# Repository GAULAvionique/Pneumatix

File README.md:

<!--"""-->

<h1 align="center">Projet Pneumatix - GAUL 2024-2025</h1>

<p align="left">

</p>

## 🌟 **Projet Pneumatix**

Pneumatix est un **module de communication et de télémétrie séparé** développé par le GAUL pour assurer un relais de données fiable entre les systèmes embarqués de la fusée et la station au sol. Conçu comme une carte fille (PCB de communication) isolée du PCB principal, le système garantit une intégrité maximale des signaux RF.

Le projet est conçu pour être :

*   Performant sur de longues distances (Module LoRa 433MHz)
*   Modulable avec un contrôle matériel des états (M0/M1) manuellement
*   Robuste face aux interférences électromagnétiques et à l'effet Doppler

L’objectif principal de Pneumatix est d'assurer une liaison de télémétrie fiable (comparée au RFD900X).

---

## 📦 **Fonctionnalités Intégrées**

Le système centralise l'infrastructure de communication externe et inclut :

*   **Communication Radio LoRa**
    Intégration du module EBYTE E22-400T33S avec routage d'antenne SMA 50 ohms pour une portée maximale et gestion des canaux LBT (Listen Before Talk).
*   **Microcontrôleur (Optionnel / Déporté)**
    Interfaçage direct avec le STM32F4 de ODBlix via des signaux logiques 3.3V natifs ou possibilité de programmer seul.
*   **Contrôle de Mode Matériel**
    Configuration des modes de fonctionnement (Normal, WOR, Configuration, Veille) via des *solder jumpers* sur les broches M0 et M1.
*   **Indicateurs de statut**
    Diagnostic visuel via des LEDs dédiées pour l'alimentation 5V et l'état d'occupation du buffer série (broche AUX).

---

## 🛰 **Architecture du Projet**

Le dépôt contient l’ensemble des éléments matériels et logiciels nécessaires au déploiement du module :

*   Schémas de conception PCB (Routage RF)
*   Scripts de configuration des registres LoRa
*   Documentation technique

---

## 📚 **Documentation**

La documentation complète des pièces du projet est disponible dans le dossier `Documentation/`.

---

## ⚙ **Compilation et Déploiement**

Le code d'interfaçage est développé autour de l’écosystème ODBLix pour communiquer avec le module.

### Compilation

```bash
git clone [https://github.com/GAULAvionique/Pneumatix.git](https://github.com/GAULAvionique/Pneumatix.git)

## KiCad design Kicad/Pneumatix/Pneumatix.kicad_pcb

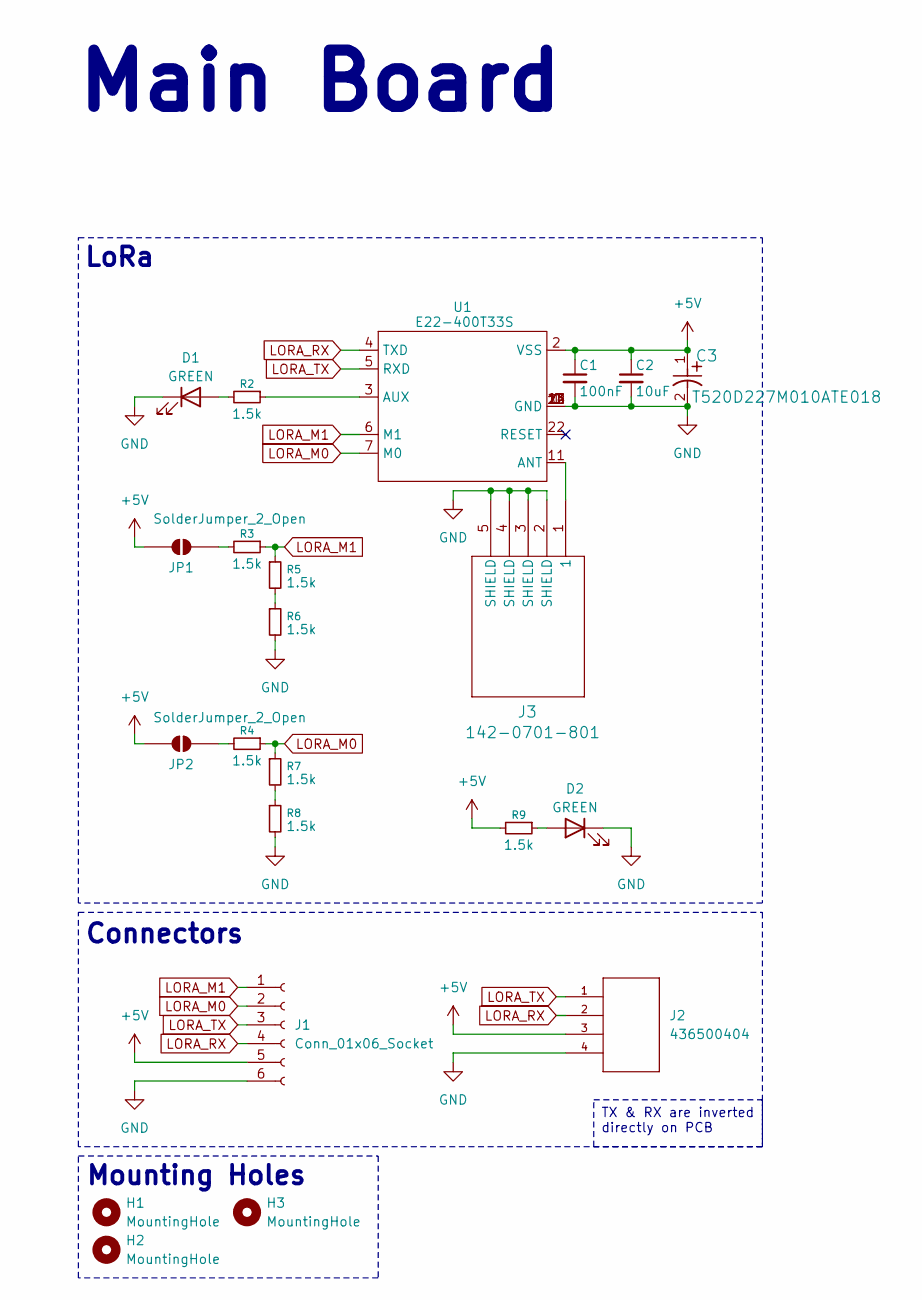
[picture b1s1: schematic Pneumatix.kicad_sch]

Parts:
C1: 100nF; C_0603_1608Metric; Manufacturer_Part_Number C0603C104K5RACTU; DigitKey_Part_Number 399-C0603C104K5RACTUCT-ND
C2: 10uF; C_0603_1608Metric; Manufacturer_Part_Number LMK107BBJ106MALT; DigitKey_Part_Number 587-3258-1-ND
C3: T520D227M010ATE018; CAPMP7.6X4.3_3.1N_KEM; Manufacturer_Part_Number T520D227M010ATE018; DigitKey_Part_Number 399-4045-1-ND
D1, D2: GREEN; LED_0603_1608Metric; Manufacturer_Part_Number LTST-C190GKT; DigitKey_Part_Number 160-LTST-C190GKTCT-ND
H1, H2, H3: MountingHole; MountingHole_3.2mm_M3
J1: Conn_01x06_Socket; PinHeader_1x06_P2.00mm_Vertical
J2: 436500404; CONN_SD-43650-002_04_MOL; MANUFACTURER_PART_NUMBER 436500404; DigitKey_Part_Number WM1877-ND
J3: 142-0701-801; CONN_142-0701-801; Manufacturer_Part_Number 142-0701-801; DigitKey_Part_Number J502-ND
JP1, JP2: SolderJumper_2_Open; SolderJumper-2_P1.3mm_Open_TrianglePad1.0x1.5mm
R2, R3, R4, R5, R6, R7, R8, R9: 1.5k; R_0603_1608Metric; Manufacturer_Part_Number RG1608P-152-B-T5; DigitKey_Part_Number RG16P1.5KBCT-ND
U1: E22-400T33S; E32-433T33S

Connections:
+5V: C1.1, C2.1, C3.1, J1.5, J2.3, JP1.2 (B), JP2.2 (B), R9.2, U1.2 (VSS)
GND: C1.2, C2.2, C3.2, D1.1 (K), D2.1 (K), J1.6, J2.4, J3.2 (SHIELD), J3.3 (SHIELD), J3.4 (SHIELD), J3.5 (SHIELD), R6.2, R8.2, U1.0 (GND), U1.1 (GND), U1.12 (GND), U1.13 (GND), U1.14 (GND), U1.23 (GND)
LORA_M0: J1.2, R4.1, R7.1, U1.7 (M0)
LORA_M1: J1.1, R3.1, R5.1, U1.6 (M1)
LORA_RX: J1.4, J2.2, U1.4 (TXD)
LORA_TX: J1.3, J2.1, U1.5 (RXD)
unnamed: D1.2 (A), R2.2
unnamed: D2.2 (A), R9.1
unnamed: JP1.1 (A), R3.2
unnamed: JP2.1 (A), R4.2
unnamed: R5.2, R6.1
unnamed: R7.2, R8.1
unnamed: J3.1, U1.11 (ANT)
unnamed: R2.1, U1.3 (AUX)

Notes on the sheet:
Connectors
Main Board
LoRa
Mounting Holes
TX & RX are inverted directly on PCB

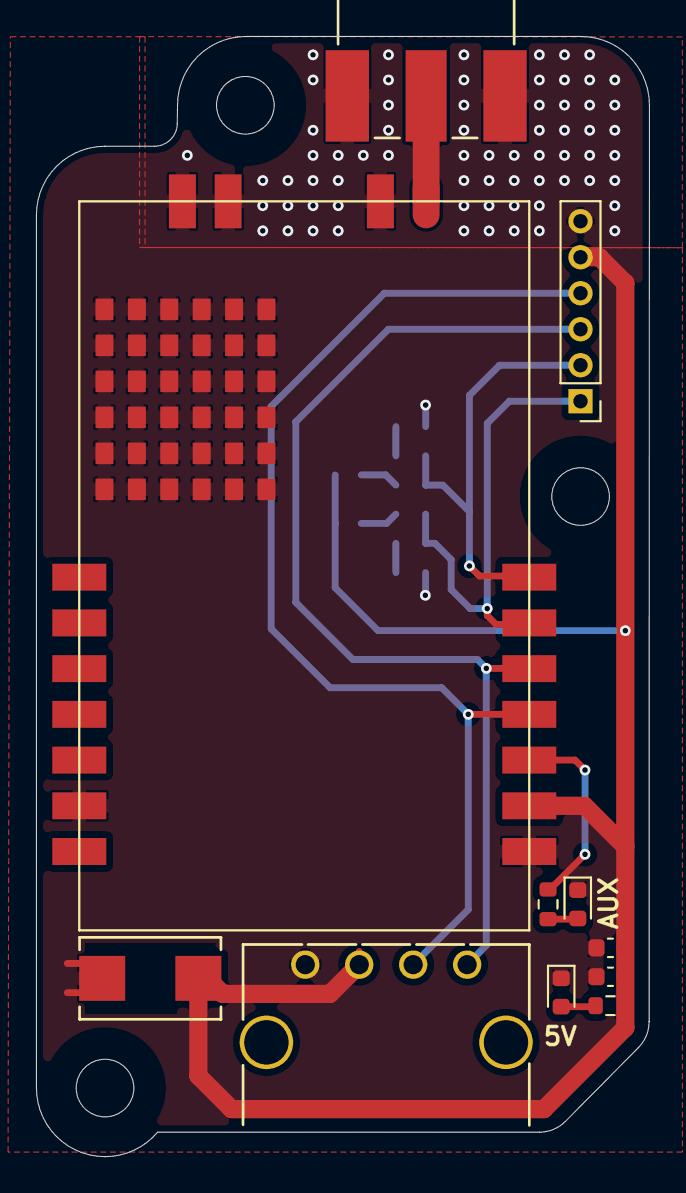
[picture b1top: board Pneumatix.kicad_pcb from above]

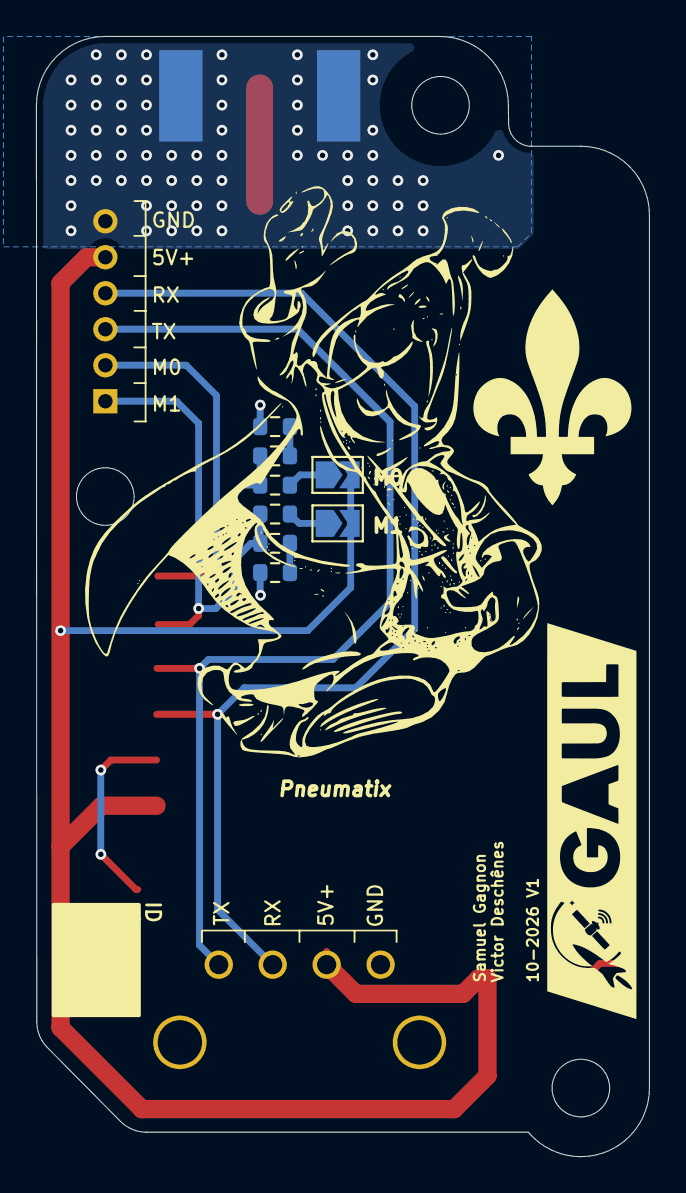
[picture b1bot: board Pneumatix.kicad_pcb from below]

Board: 2 copper layers, 34.1 x 62.2 mm, 22 parts (8 on the bottom side), 14 nets.
